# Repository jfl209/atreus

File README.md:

# atreus

QMK firmware for my Keyboardio Atreus + PS/2 TrackPoint mod.

The original firmware source was lost. This repo was rebuilt from the running
keyboard:

- `dump/atreus-flash.hex` was read off the ATmega32U4 over Caterina/avr109.
- The QMK keymap was decoded from the dump and turned back into source under
  `keyboards/atreus_trackpoint/`.
- The trackpoint daughterboard schematic was copied in from KiCad.

If you're future-me opening this cold: start with `docs/DECODING.md` (how
the keymap was recovered) and `docs/HARDWARE.md` (what's on the PCBs).

## Hardware

- Keyboardio Atreus, ATmega32U4, Caterina bootloader
- Custom trackpoint daughterboard (KiCad files in `hardware/`, gerbers in
  `hardware/gerbers/`) with:
  - IBM-style PS/2 TrackPoint module
  - 5× WS2811-driven indicator LEDs
- 3D-printed trackpoint holder (`hardware/3d-printed/atreus trackpoint
  holder v*.stl`). Iterated through 8 versions in Jan 2021 — v8 is the last,
  presumably the keeper. The originating CAD (likely Fusion 360) was not
  recovered.

## Layout

5 layers, all built on the standard 4×12 Atreus matrix:

| # | Name    | Activation        | What's on it |
|---|---------|-------------------|--------------|
| 0 | `BASE`  | default           | QWERTY |
| 1 | `SHIFT` | hold right thumb `MO(1)` | every alpha key sent as `LSFT(letter)` — thumb-driven shift |
| 2 | `NUM`   | hold left thumb `MO(2)`  | digits, brackets, shifted symbols |
| 3 | `FN`    | hold `MO(3)` from `SHIFT` | F1-F15, arrow cluster |
| 4 | `ADJ`   | hold `MO(4)` from `NUM`   | numbers + arrows combined |

Right-thumb keys are mod-tap:

- `RCTL_T(KC_QUOT)` — tap for `'`, hold for Right-Ctrl
- `RALT_T(KC_MINS)` — tap for `-`, hold for Right-Alt

Trackpoint mouse buttons are at matrix positions `[2,5]` and `[2,6]` — the
center of the third row, wired through the matrix as `KC_BTN1` / `KC_BTN2`.

See `keyboards/atreus_trackpoint/keymaps/default/keymap.c` for the full
keymap.

## Building

This repo contains only the custom keyboard folder. Drop it into a QMK
checkout to build:

```sh
# 1. Get QMK
git clone https://github.com/qmk/qmk_firmware.git
cd qmk_firmware
make git-submodule        # pulls chibios, lufa, etc.

# 2. Link in this keyboard
ln -s ~/git/atreus/keyboards/atreus_trackpoint keyboards/atreus_trackpoint

# 3. Build
qmk compile -kb atreus_trackpoint -km default
# (output: atreus_trackpoint_default.hex in the repo root)
```

**Before flashing a fresh build**, confirm the trackpoint pins in
`keyboards/atreus_trackpoint/config.h` are correct. They were guessed, not
recovered. See `docs/HARDWARE.md` § "How to verify the pins".

If a new QMK release renamed something and the build breaks, the original
firmware was built around early-2021 QMK — pin to a commit from that window
and port forward in small steps.

## Flashing

```sh
# Restore the captured backup
./flash.sh

# Or flash a fresh build
./flash.sh path/to/atreus_trackpoint_default.hex
```

To enter bootloader mode: hold `Fn+Esc` if the binding survived in your
build, otherwise press the reset button on the bottom of the keyboard —
it's accessible through a small hole in the bottom plate, poke it with a
paperclip.

## Layout of this repo

```
.
├── README.md
├── flash.sh                          # one-command flash helper
├── dump/
│   ├── atreus-flash.hex              # working firmware backup (re-flashable)
│   └── atreus-flash.bin              # raw binary, same content
├── docs/
│   ├── DECODING.md                   # how the keymap was recovered from the dump
│   └── HARDWARE.md                   # schematic notes, pin assignments, gotchas
├── hardware/
│   ├── atreus_trackpoint.{sch,kicad_pcb,pro,net,lib}
│   ├── 3d-printed/                   # printable STLs (v1-v8) of trackpoint holder
│   └── gerbers/                      # PCB fab files
├── keyboards/
│   └── atreus_trackpoint/            # QMK keyboard (symlink into qmk_firmware/keyboards)
│       ├── atreus_trackpoint.{c,h}
│       ├── config.h                  # matrix + trackpoint pin defs (TODOs!)
│       ├── rules.mk
│       ├── info.json
│       └── keymaps/default/
│           ├── keymap.c              # 5-layer keymap
│           └── rules.mk
└── tools/
    └── decode_keymap.py              # the decoder used on the dump
```

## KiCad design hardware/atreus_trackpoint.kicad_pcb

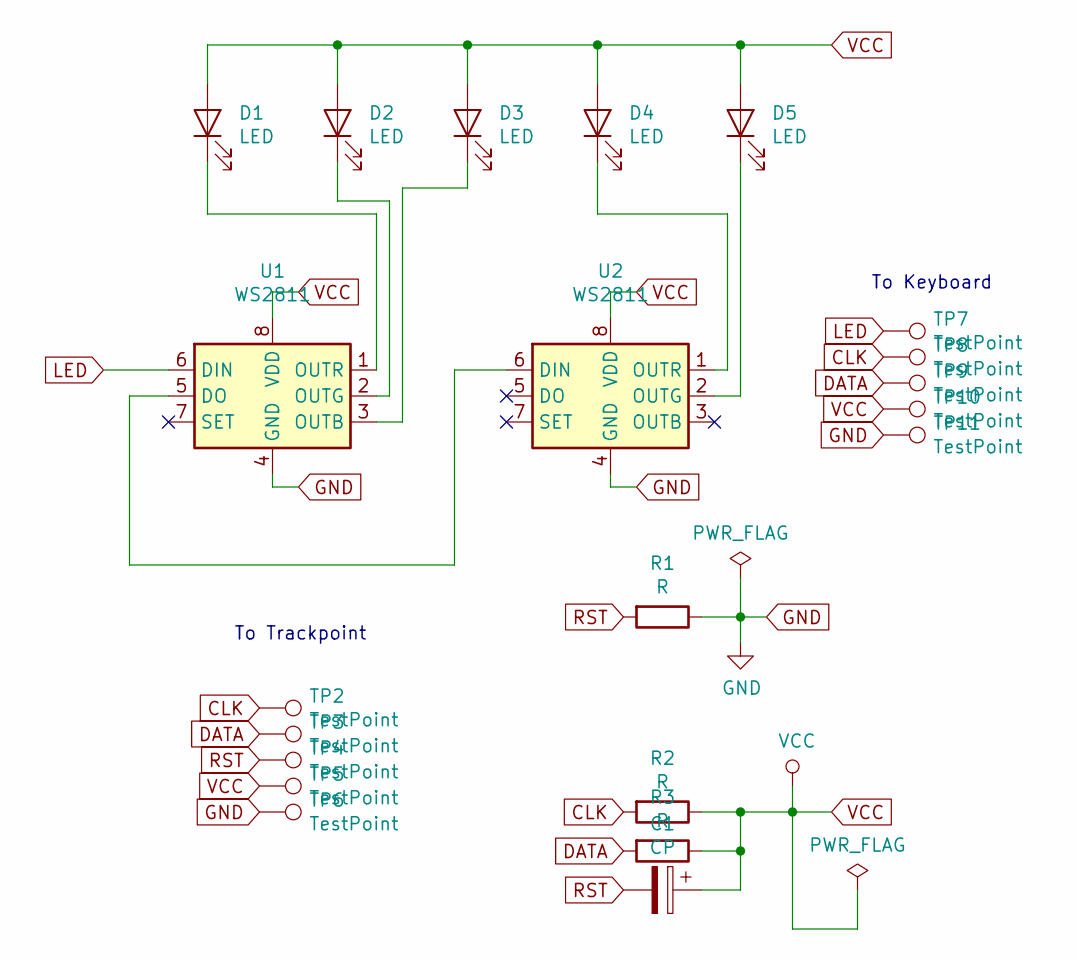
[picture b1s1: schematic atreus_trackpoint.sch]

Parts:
C1: CP; C_1206_3216Metric
D1, D2, D3, D4, D5: LED; LED_D3.0mm
R1, R2, R3: R; R_0805_2012Metric
TP2, TP3, TP4, TP5, TP6, TP7, TP8, TP9, TP10, TP11: TestPoint; TestPoint_Pad_1.0x1.0mm
U1, U2: WS2811; SOP-8_3.76x4.96mm_P1.27mm

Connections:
CLK: R2.2, TP2.1, TP8.1
DATA: R3.2, TP3.1, TP9.1
GND: R1.1, TP6.1, TP11.1, U1.4 (GND), U2.4 (GND)
LED: TP7.1, U1.6 (DIN)
unnamed: D1.1 (K), U1.1 (OUTR)
unnamed: D2.1 (K), U1.2 (OUTG)
unnamed: D3.1 (K), U1.3 (OUTB)
unnamed: D4.1 (K), U2.1 (OUTR)
unnamed: D5.1 (K), U2.2 (OUTG)
unnamed: U1.5 (DO), U2.6 (DIN)
RST: C1.2, R1.2, TP4.1
VCC: C1.1, D1.2 (A), D2.2 (A), D3.2 (A), D4.2 (A), D5.2 (A), R2.1, R3.1, TP5.1, TP10.1, U1.8 (VDD), U2.8 (VDD)

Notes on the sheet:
To Trackpoint
To Keyboard

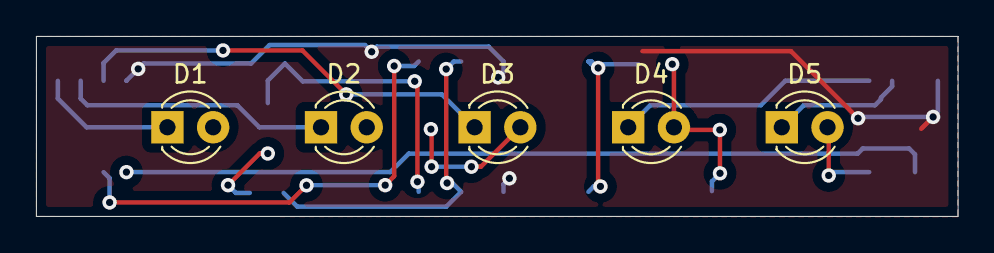
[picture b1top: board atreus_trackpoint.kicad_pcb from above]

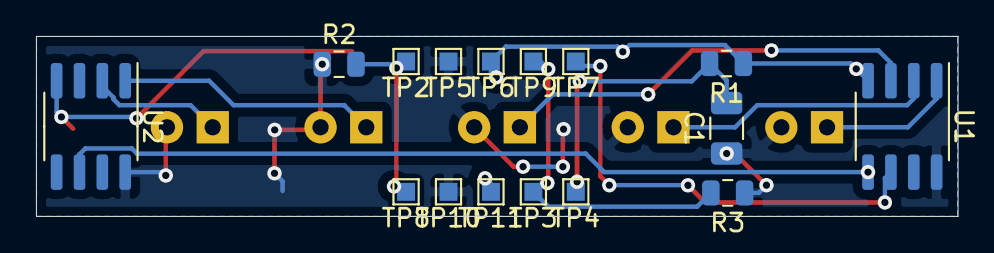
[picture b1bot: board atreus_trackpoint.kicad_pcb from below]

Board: 2 copper layers, 51.2 x 10.0 mm, 21 parts (16 on the bottom side), 12 nets.

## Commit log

2026-06-20 Initial commit: reconstructed firmware + source repo
    Source for the original QMK firmware running on my Keyboardio Atreus +
    trackpoint mod was lost. Rebuilt from the running keyboard:
    - dump/atreus-flash.hex captured off the ATmega32U4 via Caterina/avr109
    - 5-layer QMK keymap decoded out of the dump and re-emitted as source
    under keyboards/atreus_trackpoint/keymaps/default/keymap.c
    - Trackpoint daughterboard KiCad files copied in from iCloud
2026-06-20 Add 3D-printed trackpoint holder STLs, individual gerbers, and photo
    - hardware/3d-printed/: 8 STL iterations of the trackpoint holder (v8 is
    the final). The originating CAD (Fusion 360, per memory) wasn't found
    on this machine — possibly on an old laptop or never persisted to disk.
    - hardware/gerbers/: individual gerber + drill files (replaces gerber.zip)
    - docs/atreus-c64-caps.png: photo of the keyboard with C64 keycaps and
    trackpoint visible
2026-06-20 Fix reset-button instructions: accessible via hole in bottom plate
    No disassembly needed — poke through with a paperclip.
2026-06-20 Rewrite keymap to 'Mac-Natural' 3-layer layout + add printable PDF reference
    Replaces the reconstructed 5-layer keymap (which had quirky behaviors like
    LSFT-on-every-key shift layer) with a clean, ergonomic layout designed for a
    Mac + vim developer:
    - BASE: QWERTY, modifiers on thumb row, Hyper on bottom-left pinky
    - NAV (hold Bsp): arrows on HJKL, page nav, F-keys, media
    - SYM (hold Spc): numbers on home row, shifted symbols on top row, brackets
2026-06-20 Fix keymap PDF: legend on page 1 with BASE layer, not its own page
    Moved the legend above the matrix in layer 0 so it can't be orphaned to
    its own page by a Chrome page-break. PDF is now exactly 3 pages (one per
    layer).
